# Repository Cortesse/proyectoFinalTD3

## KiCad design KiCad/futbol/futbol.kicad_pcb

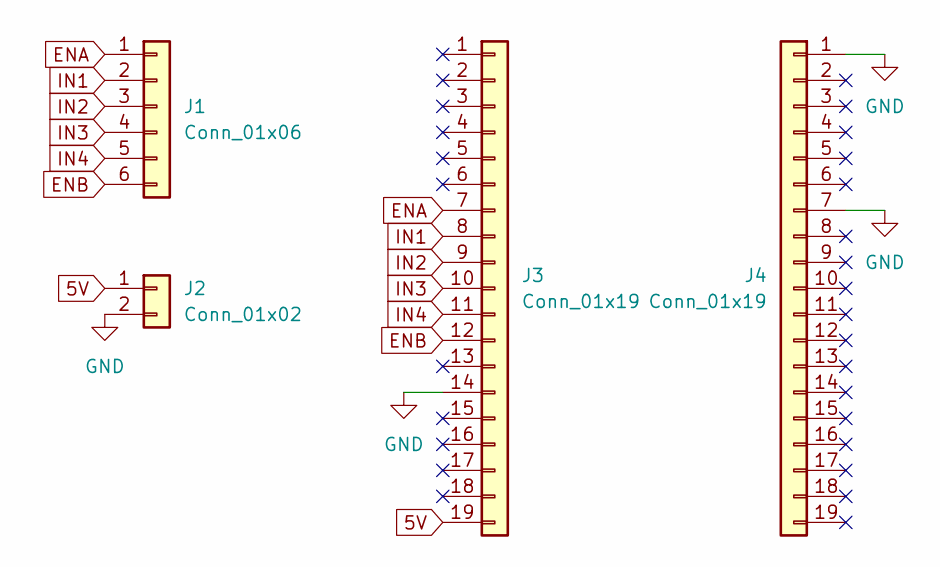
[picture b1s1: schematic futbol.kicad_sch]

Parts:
J1: Conn_01x06; PinSocket_1x06_P2.54mm_Vertical
J2: Conn_01x02; PinSocket_1x02_P2.54mm_Vertical
J3, J4: Conn_01x19; PinSocket_1x19_P2.54mm_Vertical

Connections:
5V: J2.1, J3.19
ENA: J1.1, J3.7
ENB: J1.6, J3.12
GND: J2.2, J3.14, J4.1, J4.7
IN1: J1.2, J3.8
IN2: J1.3, J3.9
IN3: J1.4, J3.10
IN4: J1.5, J3.11

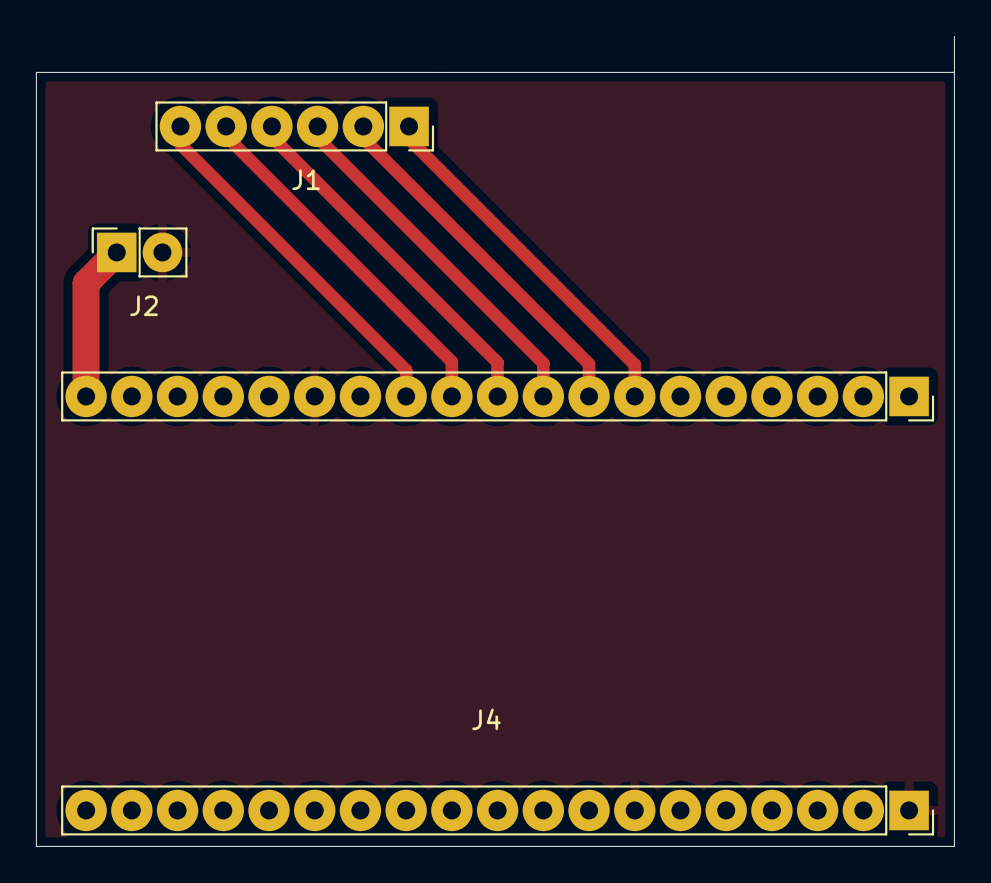
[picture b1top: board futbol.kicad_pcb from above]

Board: 2 copper layers, 51.0 x 45.0 mm, 4 parts (0 on the bottom side), 8 nets.

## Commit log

2025-11-09 main
2025-11-09 final_main
